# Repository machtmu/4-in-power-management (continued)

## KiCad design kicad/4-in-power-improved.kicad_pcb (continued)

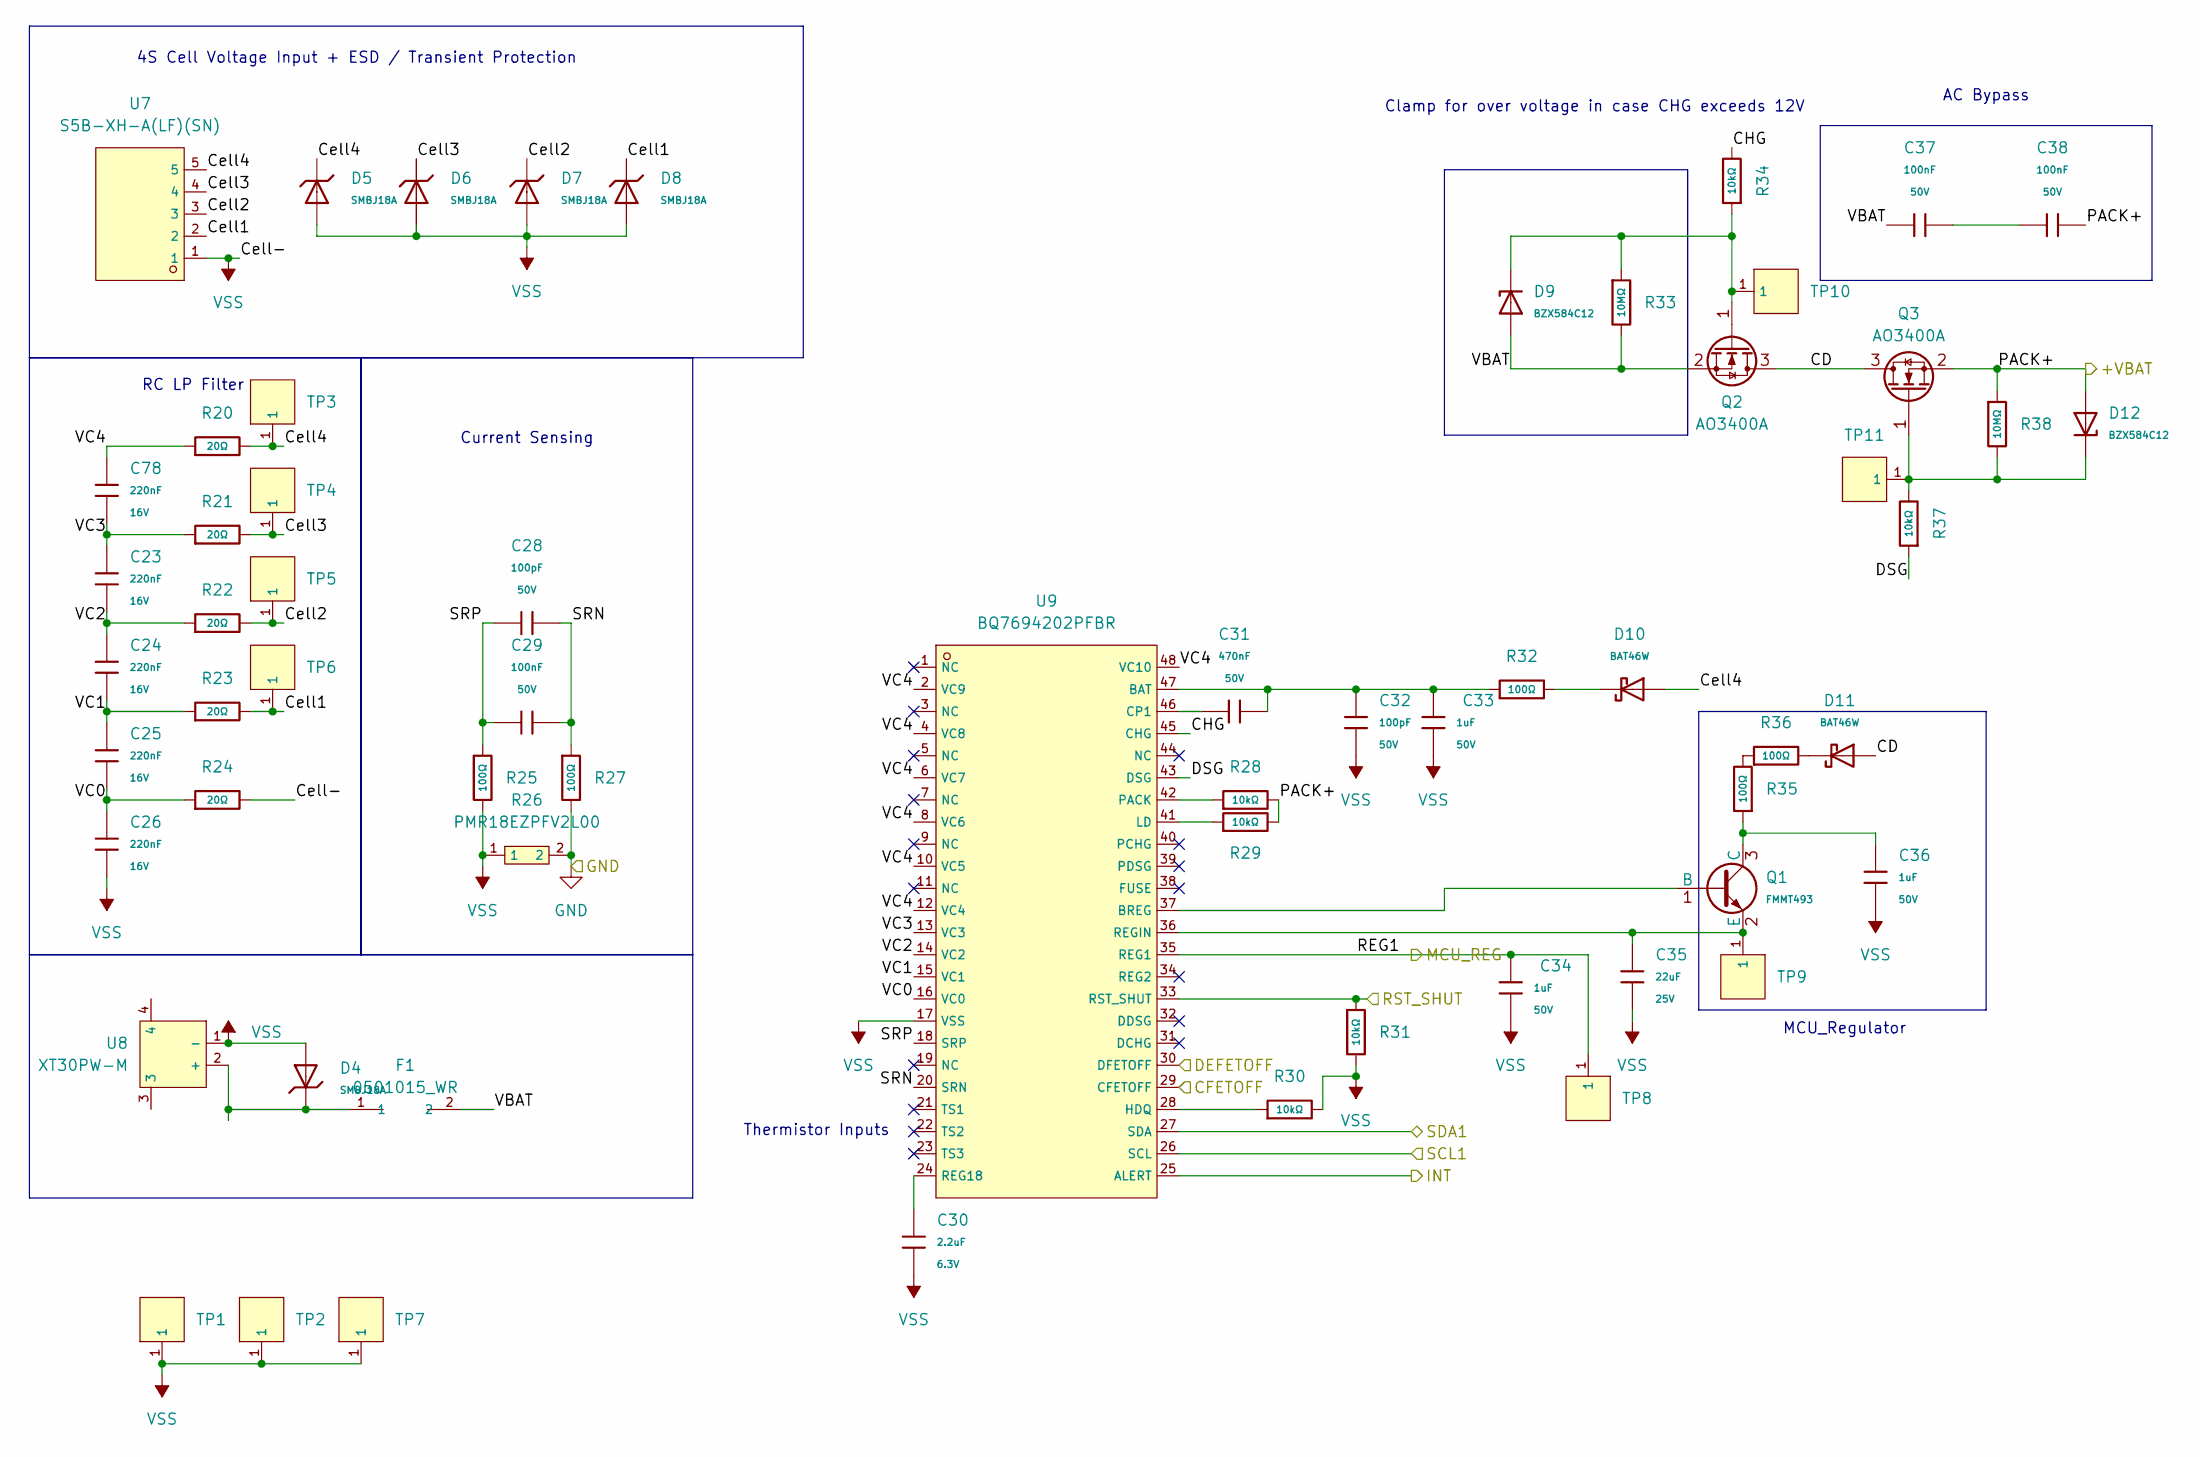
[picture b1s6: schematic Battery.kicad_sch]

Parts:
C23, C24, C25, C26, C78: 220nF; C_0402; Voltage Rated 16V; Tolerance ±10%; Part CL05B224KO5NNNC; LCSC C16772
C28, C32: 100pF; C_0402; Voltage Rated 50V; Tolerance ±5%; Part 0402CG101J500NT; LCSC C1546
C29, C37, C38: 100nF; C_0402; Voltage Rated 50V; Tolerance ±10%; Part CL05B104KB54PNC; LCSC C307331
C30: 2.2uF; C_0402; Voltage Rated 6.3V; Tolerance ±20%; Part CL05A225MQ5NSNC; LCSC C12530
C31: 470nF; C_0805; Voltage Rated 50V; Tolerance ±10%; Part CL21B474KBFNNNE; LCSC C13967
C33, C34, C36: 1uF; C_0603; Voltage Rated 50V; Tolerance ±10%; Part CL10A105KB8NNNC; LCSC C15849
C35: 22uF; C_0805; Voltage Rated 25V; Tolerance ±20%; Part CL21A226MAQNNNE; LCSC C45783
D4, D5, D6, D7, D8: SMBJ18A; D_SMB; Part SMBJ18A; LCSC C19077573
D9, D12: BZX584C12; D_SOD-523; Zener Voltage (Range) 11.4V~12.7V; Zener Voltage (Nom) 12V; Part BZX584C12; LCSC C22395579
D10, D11: BAT46W; D_SOD-123; Forward Voltage (Vf@If) 450mV@10mA; Reverse Voltage (Vr) 100V; Part BAT46W; LCSC C7420332
F1: 0501015_WR; F1206; LCSC C126815
Q1: FMMT493; Q_SOT-23; Part FMMT493; LCSC C28646275
Q2, Q3: AO3400A; SOT-23
R20, R21, R22, R23, R24: 20Ω; R_0603; Overload Voltage (Max) 75V; Tolerance ±1%; Part 0603WAF200JT5E; LCSC C22950
R25, R27, R32, R35, R36: 100Ω; R_0402; Overload Voltage (Max) 50V; Tolerance ±1%; Part 0402WGF1000TCE; LCSC C25076
R26: PMR18EZPFV2L00; R1206; LCSC C92124
R28, R29, R30, R31, R34, R37: 10kΩ; R_0402; Overload Voltage (Max) 50V; Tolerance ±1%; Part 0402WGF1002TCE; LCSC C25744
R33, R38: 10MΩ; R_0402; Overload Voltage (Max) 50V; Tolerance ±1%; Part 0402WGF1005TCE; LCSC C26082
TP1, TP2, TP3, TP4, TP5, TP6, TP7, TP8, TP9, TP10, TP11: RH-5015; SMD_RH-5015; LCSC C5199798
U7: S5B-XH-A(LF)(SN); CONN-TH_5P-P2.50_S5B-XH-A-LF-SN; LCSC C263757
U8: XT30PW-M; CONN-TH_XT30PW-M; LCSC C431092
U9: BQ7694202PFBR; TQFP-48_L7.0-W7.0-P0.50-LS9.0-TL; LCSC C3682863

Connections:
/BMSINT: U9.25 (ALERT); also elsewhere on the board
/KILL: U9.29 (CFETOFF); also elsewhere on the board
/MCU_REG: C34.1, TP8.1, U9.35 (REG1); also elsewhere on the board
/Power/Battery/CD: D11.2, Q2.3 (D), Q3.3 (D)
/Power/Battery/CHG: R34.2, U9.45 (CHG)
/Power/Battery/Cell1: D8.1, R23.2, TP6.1, U7.2
/Power/Battery/Cell2: D7.1, R22.2, TP5.1, U7.3
/Power/Battery/Cell3: D6.1, R21.2, TP4.1, U7.4
/Power/Battery/Cell4: D5.1, D10.2, R20.2, TP3.1, U7.5
/Power/Battery/DEFETOFF: U9.30 (DFETOFF)
/Power/Battery/DSG: R37.1, U9.43 (DSG)
/Power/Battery/PACK+: C38.2, D12.2, Q3.2 (S), R28.2, R29.2, R38.1; also elsewhere on the board
/Power/Battery/SRN: C28.2, C29.2, R27.1, U9.20 (SRN)
/Power/Battery/SRP: C28.1, C29.1, R25.1, U9.18 (SRP)
/Power/Battery/VBAT: C37.1, D9.2, F1.2, Q2.2 (S), R33.2
/Power/Battery/VC0: C25.2, C26.1, R24.1, U9.16 (VC0)
/Power/Battery/VC1: C24.2, C25.1, R23.1, U9.15 (VC1)
/Power/Battery/VC2: C23.2, C24.1, R22.1, U9.14 (VC2)
/Power/Battery/VC3: C23.1, C78.2, R21.1, U9.13 (VC3)
/Power/Battery/VC4: C78.1, R20.1, U9.2 (VC9), U9.4 (VC8), U9.6 (VC7), U9.8 (VC6), U9.10 (VC5), U9.12 (VC4), U9.48 (VC10)
/RST_SHUT: R31.1, U9.33 (RST_SHUT); also elsewhere on the board
/SCL1: U9.26 (SCL); also elsewhere on the board
/SDA1: U9.27 (SDA); also elsewhere on the board
GND: R26.2, R27.2; also elsewhere on the board
unnamed: C37.2, C38.1
unnamed: D10.1, R32.2
unnamed: D11.1, R36.2
unnamed: Q1.1 (B), U9.37 (BREG)
unnamed: C36.1, Q1.3 (C), R35.1
unnamed: C35.1, Q1.2 (E), TP9.1, U9.36 (REGIN)
unnamed: D9.1, Q2.1 (G), R33.1, R34.1, TP10.1
unnamed: D12.1, Q3.1 (G), R37.2, R38.2, TP11.1
unnamed: R35.2, R36.1
unnamed: D4.1, F1.1, U8.2 (+)
unnamed: C31.2, C32.1, C33.1, R32.1, U9.47 (BAT)
unnamed: C31.1, U9.46 (CP1)
unnamed: R30.1, U9.28 (HDQ)
unnamed: R29.1, U9.41 (LD)
unnamed: R28.1, U9.42 (PACK)
unnamed: C30.1, U9.24 (REG18)
VSS: C26.2, C30.2, C32.2, C33.2, C34.2, C35.2, C36.2, D4.2, D5.2, D6.2, D7.2, D8.2, R24.2, R25.2, R26.1, R30.2, R31.2, TP1.1, TP2.1, TP7.1, U7.1, U8.1 (-), U9.17 (VSS)

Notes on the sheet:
MCU_Regulator
Thermistor Inputs
4S Cell Voltage Input + ESD / Transient Protection
AC Bypass
Current Sensing
RC LP Filter
Clamp for over voltage in case CHG exceeds 12V

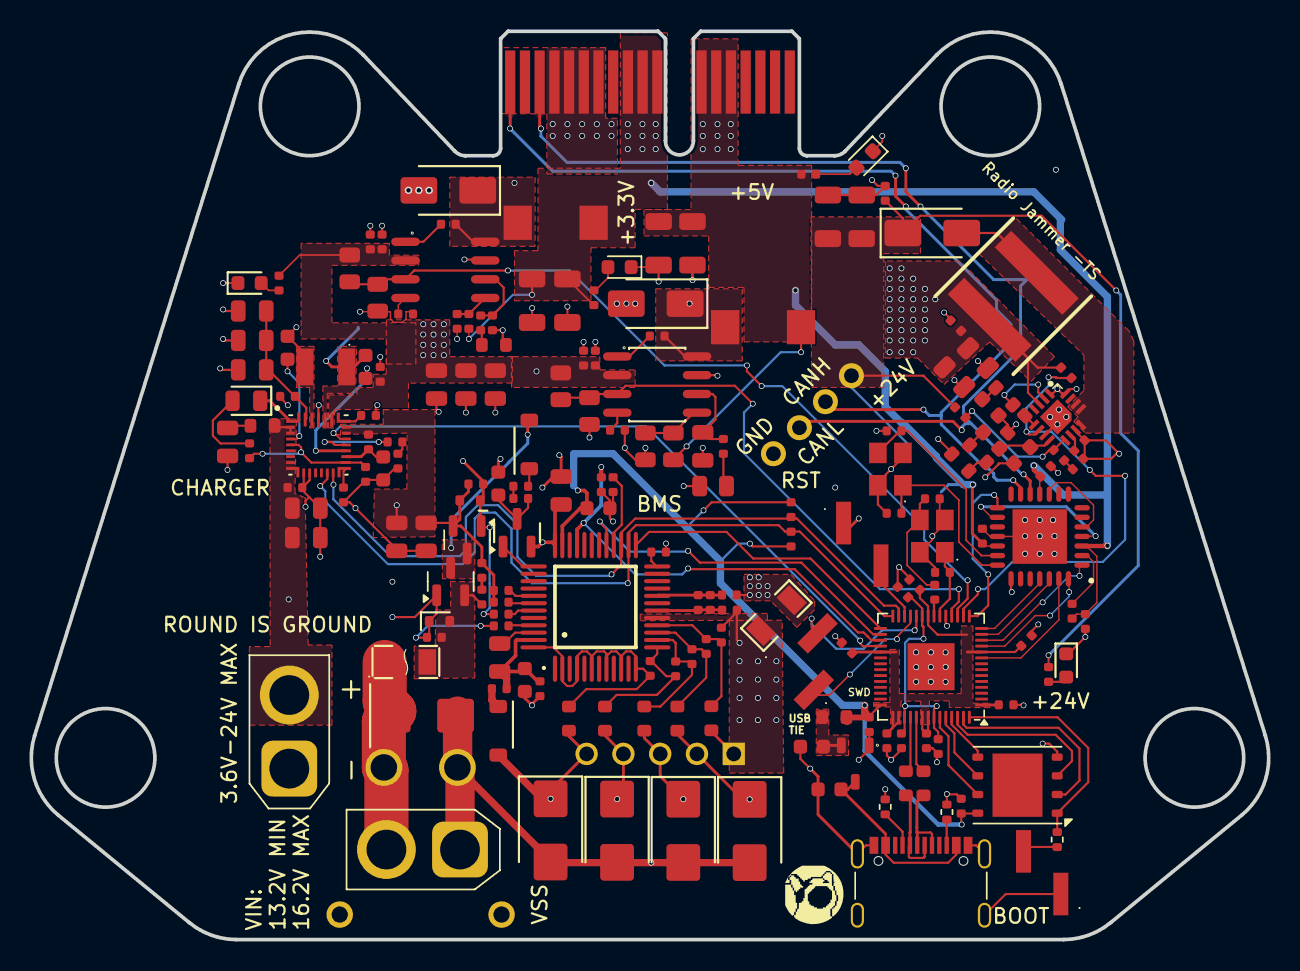
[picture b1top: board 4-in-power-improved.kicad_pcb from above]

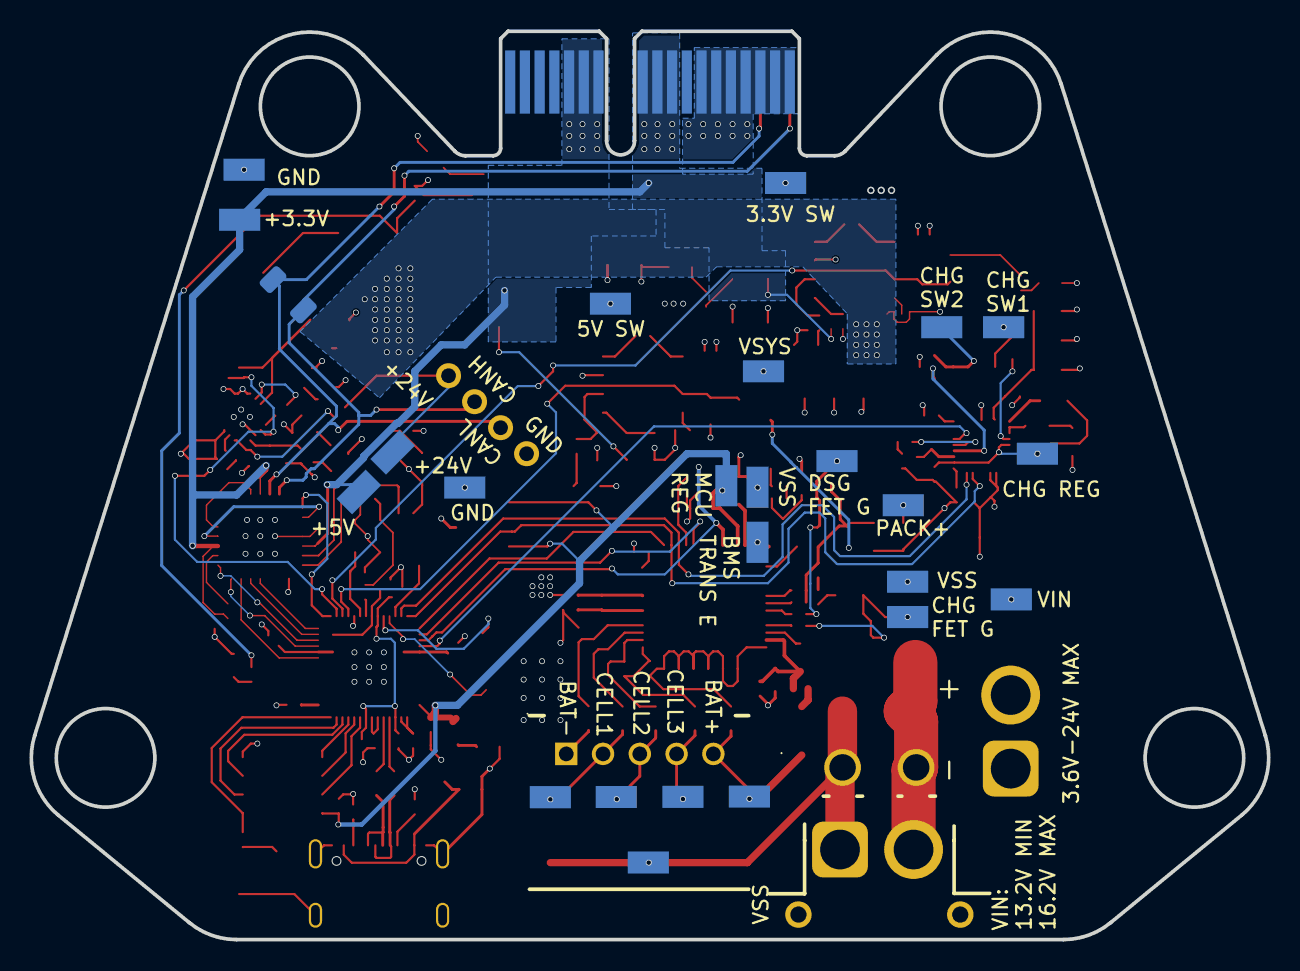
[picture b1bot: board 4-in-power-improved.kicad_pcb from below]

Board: 4 copper layers, 84.1 x 61.7 mm, 207 parts (28 on the bottom side), 124 nets.

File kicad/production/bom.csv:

Designator,Footprint,Quantity,Value,LCSC Part #
"C1, C2, C33, C34, C36, C75",C_0603,6,1uF,C15849
"C10, C17",C_0402,2,1uF,C52923
"C11, C12, C23, C24, C25, C26, C78",C_0402,7,220nF,C16772
"C13, C14, C15, C16, C18, C29, C37, C38, C46, C47, C5, C51, C6, C61, C67, C7, C74, C76, C77, C8, C81, C9",C_0402,22,100nF,C307331
C19,C_0402,1,4.7nF,C1538
C20,C_0805,1,33pF,C107115
"C21, C41",C_0402,2,1nF,C1523
C22,C_0402,1,47pF,C1567
"C27, C70",C_0805,2,1uF,C28323
"C28, C32",C_0402,2,100pF,C1546
"C3, C4",C_0402,2,15pF,C1548
C30,C_0402,1,2.2uF,C12530
C31,C_0805,1,470nF,C13967
C35,C_0805,1,22uF,C45783
"C39, C43, C44",C_0603,3,47nF,C1622
"C40, C42, C49, C50, C52, C53, C54, C55, C56, C57",C_0805,10,10uF,C440198
"C45, C58, C59, C64, C65",C_0402,5,4.7uF,C23733
C48,C_0805,1,2.2uF,C377773
"C60, C66, C73",C_0402,3,10nF,C15195
"C62, C63, C68, C69",C_1206,4,47uF,C96123
C71,C_0603,1,330pF,C1664
C72,C_0603,1,8.2nF,C1322360
"C79, C80",C_1206,2,4.7uF,C29823
"D1, D2",0603,2,LED,C2286
"D10, D11",D_SOD-123,2,BAT46W,C7420332
"D12, D9",D_SOD-523,2,BZX584C12,C22395579
D13,D_0805,1,Green,C2297
"D14, D15",D_SMA,2,SSL54,C41410770
D16,D_SMA,1,SS54,C22452
"D17, D3",D_0603,2,Yellow,C89811
"D4, D5, D6, D7, D8",D_SMB,5,SMBJ18A,C19077573
F1,F1206,1,0501015_WR,C126815
J1,USB_C_Receptacle_Palconn_UTC16-G,1,USB_C_Receptacle_USB2.0_16P,C2765186
L1,IND-SMD_L3.2-W2.5-1,1,1uH,C5159968
L2,IND-SMD_L7.5-W7.5_XAL7030,1,2.7uH,C5366402
Q1,Q_SOT-23,1,FMMT493,C28646275
"Q2, Q3",SOT-23,2,AO3400A,
"R1, R12, R13, R2",0402,4,5.1k,C25905
"R10, R9",0402,2,27,C25100
"R11, R28, R29, R30, R31, R34, R37, R40, R42, R5, R56, R57",R_0402,12,10kΩ,C25744
R14,R_0805,1,6.2kΩ,C17767
R15,R_0805,1,1.2kΩ,C17379
R16,R_0805,1,51kΩ,C17737
"R17, R41",R_0402,2,7.5kΩ,C25918
R18,R_0402,1,2.4kΩ,C25882
R19,R_0603,1,30kΩ,C22984
"R20, R21, R22, R23, R24",R_0603,5,20Ω,C22950
"R25, R27, R32, R35, R36, R39",R_0402,6,100Ω,C25076
R26,R0805,1,5mΩ,C92742
"R3, R4, R7",0402,3,1k,C11702
"R33, R38",R_0402,2,10MΩ,C26082
R43,R_0402,1,2.2kΩ,C25879
R44,R_0603,1,2Ω,C22977
"R45, R47",R_0805,2,330kΩ,C17629
"R46, R48",R_0805,2,100kΩ,C149504
"R49, R50",R_0603,2,470Ω,C23179
R51,R_0603,1,9.1kΩ,C23260
R52,R_0603,1,5.1Ω,C25197
R53,R_0402,1,47kΩ,C25792
R54,R_0402,1,2kΩ,C4109
R55,R_0402,1,47Ω,C25118
R6,R_0603,1,0Ω,C21189
R8,R_0402,1,1kΩ,C11702
"TP1, TP10, TP11, TP12, TP13, TP14, TP15, TP16, TP17, TP18, TP19, TP2, TP20, TP21, TP22, TP23, TP24, TP3, TP4, TP5, TP6, TP7, TP8, TP9",SMD_RH-5015,24,RH-5015,C5199798
U1,SOT-23-3_L2.9-W1.6-P1.90-LS2.8-BR,1,XC6206P332MR,C5446
U10,IC_BQ25672RQMR,1,BQ25672RQMR,C3682029
"U11, U13",SOIC-8_L5.0-W4.0-P1.27-LS6.0-BL,2,TPS54331DR,C9865
"U12, U14",IND-SMD_L5.4-W5.2_SLO0530H6R8MTT,2,6.8uH,C325965
U15,WQFN-16_L3.0-W3.0-P0.50-TL-EP1.7,1,LM5157RTER,C5219222
"U17, U2, U4",HDR-SMD_2P-P2.54-V-M-S4.8_DZ254S-11-02-50,3,2P SMD 2.54P Jumper,C17702633
U3,WSON-8-1EP_6x5mm_P1.27mm_EP3.4x4.3mm,1,W25Q128JVP,C190862
U5,QFN-28_L6.0-W6.0-P0.65-BL-EP3.7,1,MCP25625T-E/ML,C191253
U6,QFN-56-1EP_7x7mm_P0.4mm_EP3.2x3.2mm,1,RP2040,C2040
U7,CONN-TH_5P-P2.50_S5B-XH-A-LF-SN,1,S5B-XH-A(LF)(SN),C263757
U8,CONN-TH_XT30PW-M,1,XT30PW-M,C431092
U9,TQFP-48_L7.0-W7.0-P0.50-LS9.0-TL,1,BQ7694202PFBR,C3682863
X1,CRYSTAL-SMD_4P-L3.2-W2.5-BL,1,ABM8-272-T3,C20625731
Y1,CRYSTAL-SMD_4P-L3.2-W2.5-BL,1,X322516MLB4SI,C12668

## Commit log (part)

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2025-09-11 Version 1.0.0 of 4S Power Management Unit
2025-09-11 Bucks assigned to nicholas
2025-09-12 3.3V and 5V buck regulator layout
2025-09-12 Charger IC footprint routed RP2040 routed BMS routed xt30s and balancers router
2025-09-13 add kicad image exporter workflow
2025-09-13 Update images
2025-09-13 Footprint routing completed
2025-09-13 Remapped as much of the 3d models I could
2025-09-13 Silk screen UI changes
2025-09-13 Update README with project details and functionality
    Expanded the README to include a project overview, functionality description, and TODOs for the 4 Inch Power Management Subsystem. Moved the workflow badge to the end and added context about the desi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
2025-09-13 Update README with formatting fixes and authors
    Corrected formatting and added author credits to README.
2025-09-13 Fix formatting issues in README.md
2025-09-13 Fix formatting of Authors section in README
2025-09-15 Replace R26 with R1206 footprint and update PCB
    Replaced the R26 resistor from an R0805 to an R1206 footprint in the PCB layout and netlist, updated associated tracks and vias, and added the new R1206 footprint file. Updated schematic, BOM, design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
2025-09-15 Fixed all silk screen solder mask issues, switched 24V Xt30 connector to JST 4P with CAN lines. Board is production ready
